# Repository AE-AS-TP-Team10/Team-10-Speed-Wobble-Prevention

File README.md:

# Team-10-Speed-Wobble-Prevention
This is all of the software and CAD files for our senior project
PCB-Gerber Files is all of our gerber files we went through to make our PCB using Eaglecad and CircuitPRO
Working Code Directory is all of our libraries and our working code

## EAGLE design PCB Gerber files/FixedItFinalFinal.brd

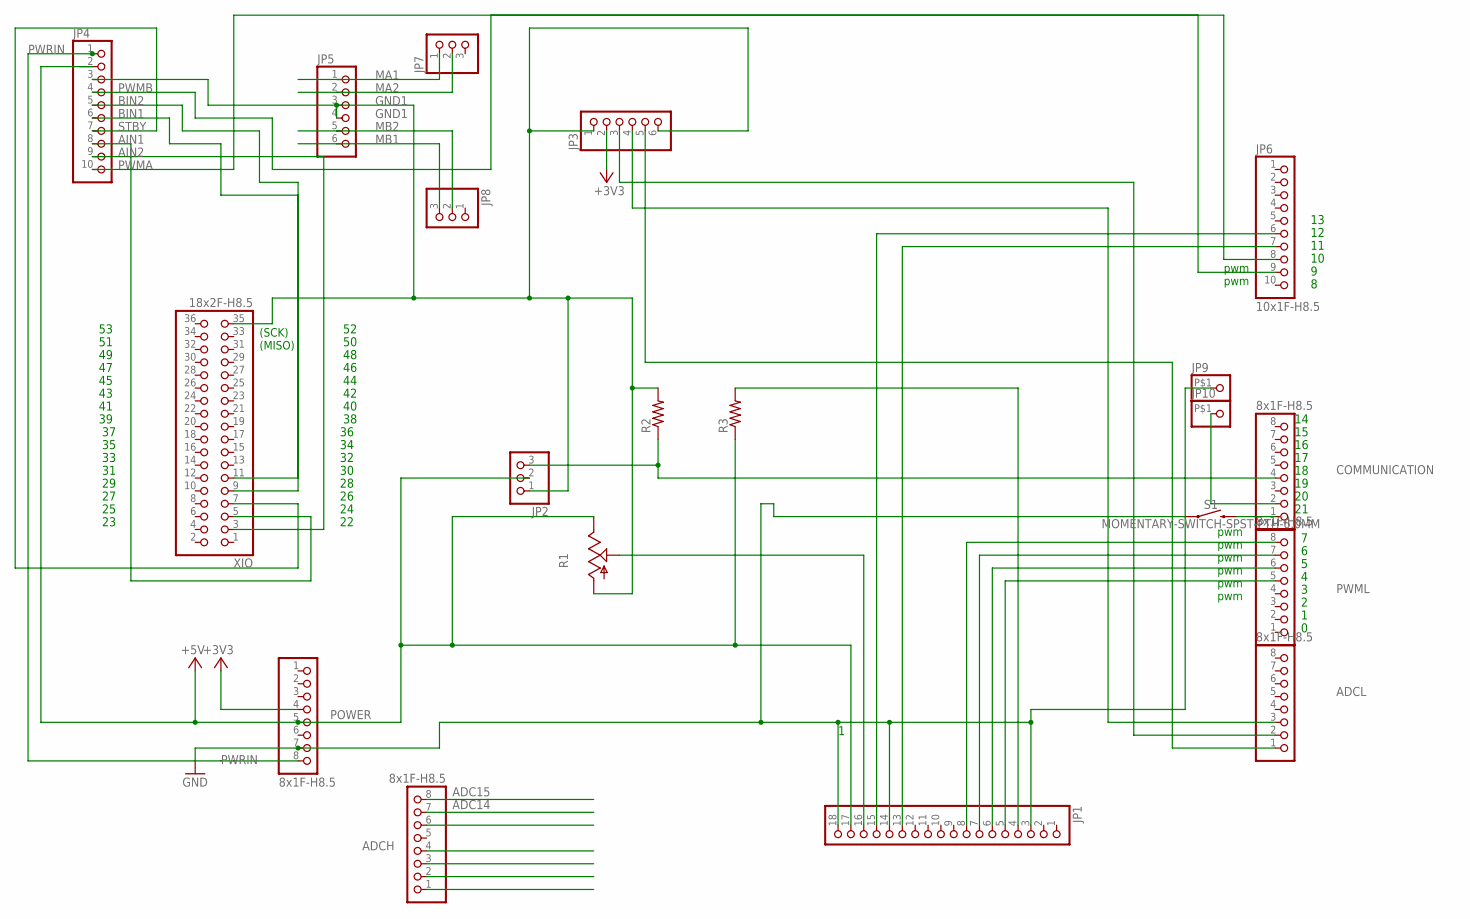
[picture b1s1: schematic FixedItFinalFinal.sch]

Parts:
ADCH: 8x1F-H8.5; 1X08
ADCL: 8x1F-H8.5; 1X08
COMMUNICATION: 8x1F-H8.5; 1X08
JP1: PINHD-1X18; 1X18
JP2, JP7, JP8: PINHD-1X3; 1X03
JP3: PINHD-1X6; 1X06
JP4: HEADER-1X10THICKER; 1X10_ROUND_76
JP5: PINHD-1X6CB; 1X06-CLEANBIG
JP6: 10x1F-H8.5; 1X10
JP9, JP10: PINHD-1X1-BIGPOGO; 1X1-BIGPOGO
POWER: 8x1F-H8.5; 1X08
PWML: 8x1F-H8.5; 1X08
R1: TRIM_US-RS3; RS3
R2, R3: R-US_0204/7; 0204/7
S1: MOMENTARY-SWITCH-SPST-PTH-6.0MM; TACTILE_SWITCH_PTH_6.0MM
XIO: 18x2F-H8.5; 2X18

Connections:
+3V3: JP3.2, POWER.4
+5V: JP1.17, JP2.2, JP4.2, POWER.5, R1.E, R3.1
ADC8: ADCH.1
ADC9: ADCH.2
ADC10: ADCH.3
ADC11: ADCH.4
ADC13: ADCH.6
ADC14: ADCH.7
ADC15: ADCH.8
AIN1: JP4.8, XIO.5
AIN2: JP4.9, XIO.3
BIN1: JP4.6, XIO.9
BIN2: JP4.5, XIO.11
GND: JP1.3, JP1.14, JP1.18, JP9.P$1, POWER.7, S1.1
GND1: JP2.1, JP3.1, JP3.6, JP4.3, JP5.3, JP5.4, R1.A, R2.2, XIO.35
MA1: JP5.1, JP7.1
MA2: JP5.2, JP7.2
MB1: JP5.6, JP8.3
MB2: JP5.5, JP8.2
unnamed: JP1.5, PWML.5
unnamed: JP1.6, PWML.6
unnamed: JP1.7, PWML.7
unnamed: JP1.8, PWML.8
unnamed: JP1.13, JP6.7
unnamed: JP1.15, JP6.6
unnamed: JP1.16, R1.S
unnamed: ADCL.1, JP3.5
unnamed: JP1.4, R3.2
unnamed: COMMUNICATION.1, S1.3 (2)
unnamed: ADCL.2, JP3.3
unnamed: ADCL.3, JP3.4
unnamed: COMMUNICATION.2, JP10.P$1
unnamed: COMMUNICATION.4, JP2.3, R2.1
PWMA: JP4.10, JP6.8
PWMB: JP4.4, JP6.9
PWRIN: JP4.1, POWER.8
STBY: JP4.7, XIO.7

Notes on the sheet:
pwm
(SCK)
(MISO)

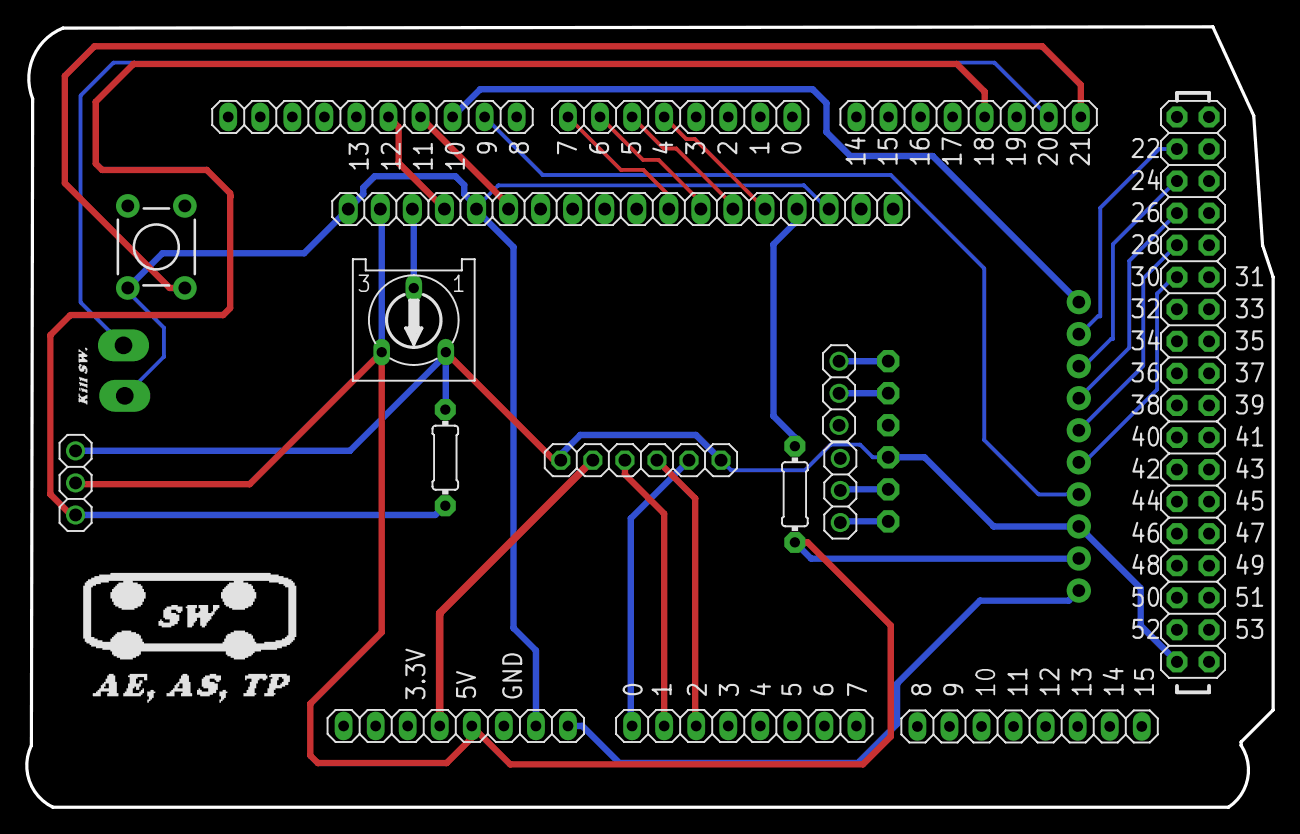
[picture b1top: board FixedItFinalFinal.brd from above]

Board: 2 copper layers, 98.8 x 61.8 mm, 20 parts (0 on the bottom side), 30 nets.

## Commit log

2023-04-14 Add files via upload
    This is all of our Arduino code for the speed wobble prevention device
2023-04-14 Add files via upload
    This is all of the models and iterations of our PCB

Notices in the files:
parts and their libraries:
SparkFun-Switches: Licensing: Creative Commons ShareAlike 4.0 International - https://creativecommons.org/licenses/by-sa/4.0
